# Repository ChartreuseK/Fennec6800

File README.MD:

# Fennec 6800
A Motorola 6800 Based Expandable Single Board Computer

## Introduction
The Fennec 6800 is a Motorola 6800 based single board computer (SBC) created with the inspiration of targeting 1977 components and features. It features an original Motorola 6800 processor running at whopping 921.6kHz, 8kB of the latest 2114 SRAM, 2kB of ROM using the brand new 2716 EPROM, and dual serial ports. An optional 40 pin expansion bus allows for connectivity to other modules, such as the Fennec VTI video terminal interface board, or to create your own attachments.

## Specifications
* Motorola 6800 @ 921.6kHz
* 1-8kB of onboard SRAM using pairs of 2114 (1k x 4 bit) SRAM chips. Using the optional RAM adapter board up to 32kB of RAM can be fitted with minimal modifications
* 2kB, 2716 EPROM containing the Fennec Monitor. Optional support for a 4kB 2732 EPROM
* Dual 6850 ACIA, RS-232 UART connected to dual 25 pin EIA-232 ports in DTE wiring.
* Selectable serial baud rates via DIP switches from 600-9600 baud + 115,200 in default /16 mode, 150-2400+28,800 in /64 mode when configured. Non-standard baud rates are possible using a different master oscillator, but CPU speed will be affected.
* Single rail design. Requires only a 5v regulated source of power.
* 40 pin expansion bus with pre-decoded expansion board select signals, allowing for quite prototyping of custom expansions.
* Beautiful blue PCB with exposed traces for a refined look.
* Compact Board design, only 8.6×5.2 inches!

The Fennec 6800 includes a capable and expandable ROM monitor built in, requiring no tedious toggling of front panel switches to enter and begin executing code. Only a terminal is required to begin making use of the system, simply hook the terminal up to the bottom serial port (furthest from the power jack). This serial port is the local console port in the default system, all traffic is normally routed through this port, though inside the monitor certain commands may be redirected to the auxiliary port located above it.

The monitor provides facilities for examining memory, depositing values into memory, jumping to code in memory, receiving a binary over the XMODEM protocol into RAM, and dumping a block of RAM over the XMODEM protocol. With these facilities and an appropriate host system, program development can be done remotely and loaded into the Fennec to speed up initial system bring-up and testing, or development can be done in the traditional way on paper then loaded in in hexadecimal into the program memory and tested out using the computer.

The monitor also provides support for option ROMs. These option ROM images can be mapped into any of the expansion regions in upper memory starting at a multiple of 0x1000. If detected they can hook into the monitor to provide future expandability and extra features, such as the Fennec VTI board which uses an option ROM to redirect the default terminal from the first serial port to a video display and asci keyboard interface, allowing for standalone use. Future cards may also use this facility to add additional commands such as providing for a rudimentary disk operation system for example.

## Manual
The file Fennec6800_Manual.pdf contains a more comprehensive manual of the Fennec, including some theory of operation as well as assembly hints and guides. Importantly if building a REV 0 board the bodeges required for correct operation are described. The primary bodge required is changing how the data bus buffer is selected, instead of being controlled by only the CPU it is decoded in a way to allow expansion boards to enable the buffer. The KiCAD schematics reflect the changes already made, however the gerbers and rev0 pcb file don't contain the fix.

## BOM 
The complete BOM can be found in either the manual, or in the spreadsheet Fennec6800_BOM.csv 
The BOM contains the reference designators, quantity, a description of the part, as well as one or more suitable Digikey part numbers. The CPU, ACIA/UARTs, and 2716/28C16 EPROM/EEPROM however need to be aquired from secondary sources as they have not been manufactured in some time. The CPU needs to be a MC6800 or direct compatible, note a 6802 has a different pinout and is not drop in compatible. The ACIAs are MC68B50 or similar UARTs, the B variant is not needed for the lower speeds, however a Hitachi 63B50 (2MHz rated) would be required for 115,200 board operation to not be overclocking the chip slightly. This speed however is honestly faster than the Fennec 68000 is really designed for, and at 9600 baud any variant is fine. For the EPROM any speed grade 2716 or 28C16 or equivalent 2kB (8-bit) EPROM/EEPROM is suitable. 2732 EPROMs may also be used, and the extra space can be mapped by installing the jumper next to the ROM socket, however the monitor would need to be reassembled to take advantage of the extra space.

## Burning the ROM
The 2716 EPROM on the Fennec 6800 should be burned with the file `software/monitor/monitor.bin`. This file is in a flat binary format suitable for burning onto a 2kB EPROM. If your program needs Intel HEX or Motorola SREC format it will need to be converted first. The ORG address is F800 (upper 2kB of address space). 

2716 EPROMs are single supply EPROMs, however they need a programmer capable of a 26v programming voltage. The common TL866CS/A is only capable of 21v, and the newer TL866II+ is only capable of 18v max, and won't be able to program the EPROM. For a more convient option there exists the 28C16 EEPROM which is pin compatible and can be programmed with only 5v and is suitable for either TL866 programmer, or even possibly with an Arduino and some custom code. The 28C16 is no-longer newly manufactured but can be fairly readilly sourced. Alternatively using a pin adapter a 28-pin 28C64 (still sold new on Digikey/Mouser from Atmel) can be converted to the 28C16 24-pin pinout. 

## Assembling the Monitor
The monitor source code is designed to be assembled with the cross-platform [AS macro assembler](http://john.ccac.rwth-aachen.de:8000/as/). It may be possible to assemble with other assemblers supporting the 6800, but some changes to the local label syntax may be required. The output of the macro assembler is it's own p file format which can then be converted using p2bin or p2hex to a suitable output format.

    asl -L monitor.asm && p2bin monitor.p
## Expansions

### 62256 RAM Adapter
In the folder Fennec 62256 RAM Adapter you can find a second PCB which allows the use of common and still in production 62256 (32k x 8) SRAM chips in place of the vintage and hard to source 2114 sram that the Fennec is designed for. This board slots into the top two ram sockets as well as the 74LS138 socket to provide the full 8kB of RAM that the board is designed for. Optionally A13 and A14 may be run to this adapter board to give the Fennec 32kB of RAM, more than normally designed for. 

### Fennec VTI
The [Fennec VTI](https://github.com/ChartreuseK/Fennec6800_VTI) is a 64x16 line text terminal interface with parallel ascii keyboard to provide a local terminal for the Fennec. It negates the need for an external serial terminal, or terminal emulator, making the Fennec into a self contained system. Using the extra port on the PIA on this card, combined with protoboard space, also allows it to be used for experimentations and developing hardware.

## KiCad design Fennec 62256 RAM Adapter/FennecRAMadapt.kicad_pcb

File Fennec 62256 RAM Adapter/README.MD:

# Fennec 6800 62256 RAM Adapter

This adapter allows the use of common 62256 32k x 8-bit SRAM chips with the Fennec 6800, replacing the vintage 2114 SRAM chips. The adapter plugs into the top two SRAM sockets as well as the 74LS138 socket (replacing the IC) and provides a full 8kB of SRAM to the Fennec. Optionally wires may be soldered down to the main board to grab A13 and A14 and soldered to the ram adapter. This modification would allow for the maximum of 32kB of RAM to be fitted to the system, more than normally possbile.

BOM:

* 1x 62256 SRAM - DIP 28
* 1x 74LS02 - DIP 14
* 1x 74LS08 - DIP 14
* 3x 0.1uF 50v X7R Ceramic Capacitors 0.1" pin spacing
* 2x 1k ohm 1/4W carbon film resistor, through hole
* 2x 1x40 pin male machine pin breakaway header. 
  * (16 + 18 + 18 + 9) = 61 pins required.
* Optional 1x40 male square pin header for jumpers. 2 + 3 + 3
* Optional 3x jumper shorting connectors
* 2x DIP 14 socket
* 1x DIP 28 wide (0.6") socket

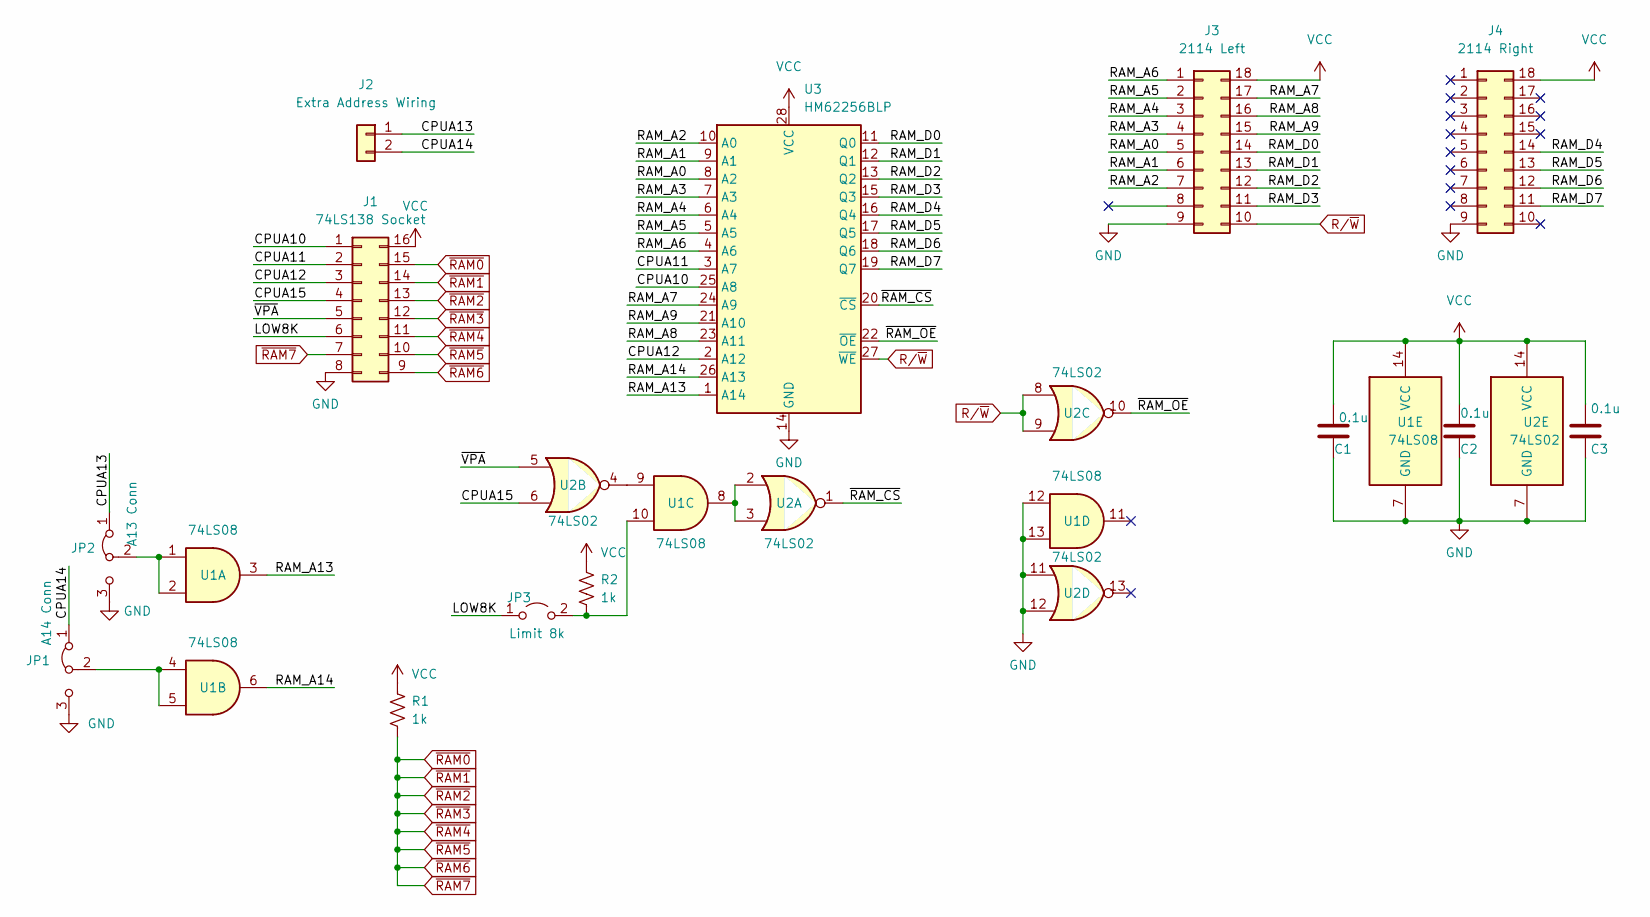
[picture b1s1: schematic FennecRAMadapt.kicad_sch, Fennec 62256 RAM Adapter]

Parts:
C1, C2, C3: 0.1u; C_Disc_D3.0mm_W1.6mm_P2.50mm
J1: 74LS138 Socket; DIP-16 Copper Ref Pin 1 Mark
J2: Extra Address Wiring; PinHeader_1x02_P2.54mm_Vertical
J3: 2114 Left; DIP-18 Copper Ref Pin 1 Mark
J4: 2114 Right; DIP-18 Copper Ref Pin 1 Mark
JP1: A14 Conn; PinHeader_1x03_P2.54mm_Vertical
JP2: A13 Conn; PinHeader_1x03_P2.54mm_Vertical
JP3: Limit 8k; PinHeader_1x02_P2.54mm_Vertical
R1, R2: 1k; R_Axial_DIN0207_L6.3mm_D2.5mm_P10.16mm_Horizontal
U1: 74LS08; DIP-14 Copper Ref Pin 1 Mark
U2: 74LS02; DIP-14 Copper Ref Pin 1 Mark
U3: HM62256BLP; DIP-28 Copper Ref Pin 1

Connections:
/CPUA10: J1.1, U3.25 (A8)
/CPUA11: J1.2, U3.3 (A7)
/CPUA12: J1.3, U3.2 (A12)
/CPUA13: J2.1, JP2.1 (A)
/CPUA14: J2.2, JP1.1 (A)
/CPUA15: J1.4, U2.6
/LOW8K: J1.6, JP3.1 (A); also elsewhere on the board
/RAM_A0: J3.5, U3.8 (A2)
/RAM_A1: J3.6, U3.9 (A1)
/RAM_A2: J3.7, U3.10 (A0)
/RAM_A3: J3.4, U3.7 (A3)
/RAM_A4: J3.3, U3.6 (A4)
/RAM_A5: J3.2, U3.5 (A5)
/RAM_A6: J3.1, U3.4 (A6)
/RAM_A7: J3.17, U3.24 (A9)
/RAM_A8: J3.16, U3.23 (A11)
/RAM_A9: J3.15, U3.21 (A10)
/RAM_A13: U1.3, U3.1 (A14)
/RAM_A14: U1.6, U3.26 (A13)
/RAM_D0: J3.14, U3.11 (Q0)
/RAM_D1: J3.13, U3.12 (Q1)
/RAM_D2: J3.12, U3.13 (Q2)
/RAM_D3: J3.11, U3.15 (Q3)
/RAM_D4: J4.14, U3.16 (Q4)
/RAM_D5: J4.13, U3.17 (Q5)
/RAM_D6: J4.12, U3.18 (Q6)
/RAM_D7: J4.11, U3.19 (Q7)
/~RAM_CS: U2.1, U3.20 (~CS)
/~RAM_OE: U2.10, U3.22 (~OE)
/~VPA: J1.5, U2.5
GND: C1.2, C2.2, C3.2, J1.8, J3.9, J4.9, JP1.3 (B), JP2.3 (B), U1.7 (GND), U1.12, U1.13, U2.7 (GND), U2.11, U2.12, U3.14 (GND)
unnamed: JP1.2 (C), U1.4, U1.5
unnamed: JP2.2 (C), U1.1, U1.2
unnamed 33: JP3.2 (B), R2.2, U1.10; also elsewhere on the board
unnamed: U1.8, U2.2, U2.3
unnamed: U1.9, U2.4
R/~W: J3.10, U2.8, U2.9, U3.27 (~WE)
VCC: C1.1, C2.1, C3.1, J1.16, J3.18, J4.18, R1.1, R2.1, U1.14 (VCC), U2.14 (VCC), U3.28 (VCC)
~RAM7: J1.7, J1.9, J1.10, J1.11, J1.12, J1.13, J1.14, J1.15, R1.2

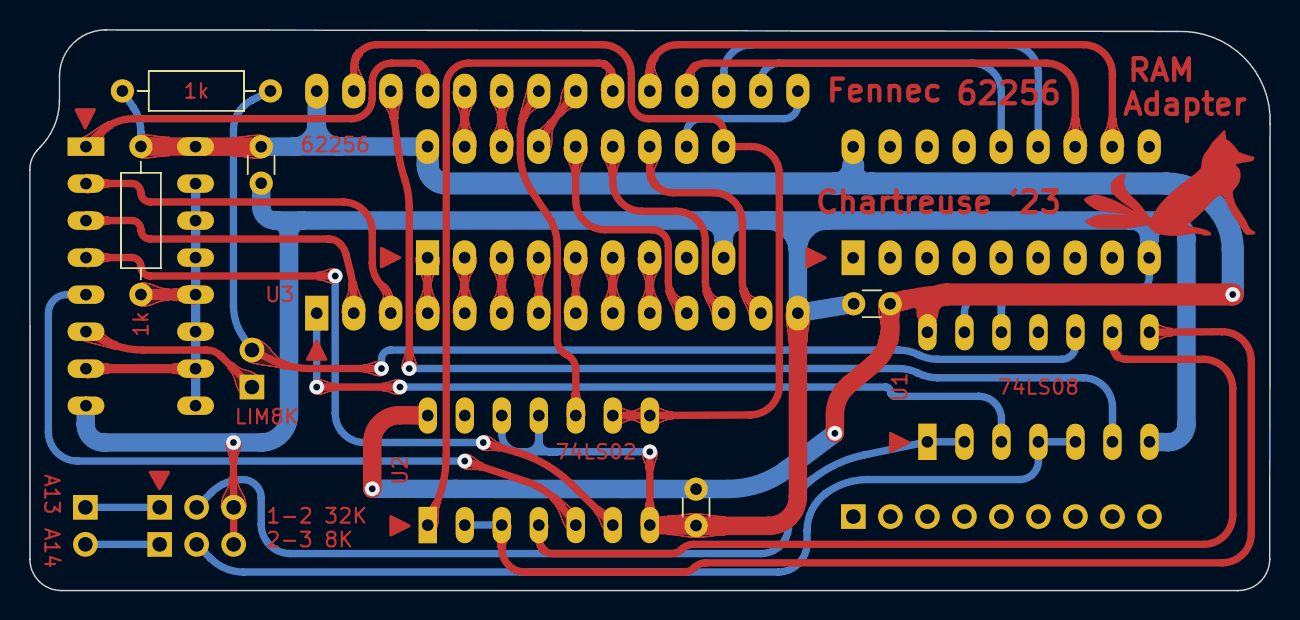
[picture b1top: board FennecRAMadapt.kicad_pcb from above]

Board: 2 copper layers, 85.1 x 38.5 mm, 16 parts (0 on the bottom side), 39 nets.

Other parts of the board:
LIM8K: Limit 8k; PinHeader_1x02_P2.54mm_Vertical
P1: Mounting Support DNC; PinHeader_1x09_P2.54mm_Vertical

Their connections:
/LOW8K: LIM8K.1 (A); also elsewhere on the board
unnamed 33: LIM8K.2 (B); also elsewhere on the board

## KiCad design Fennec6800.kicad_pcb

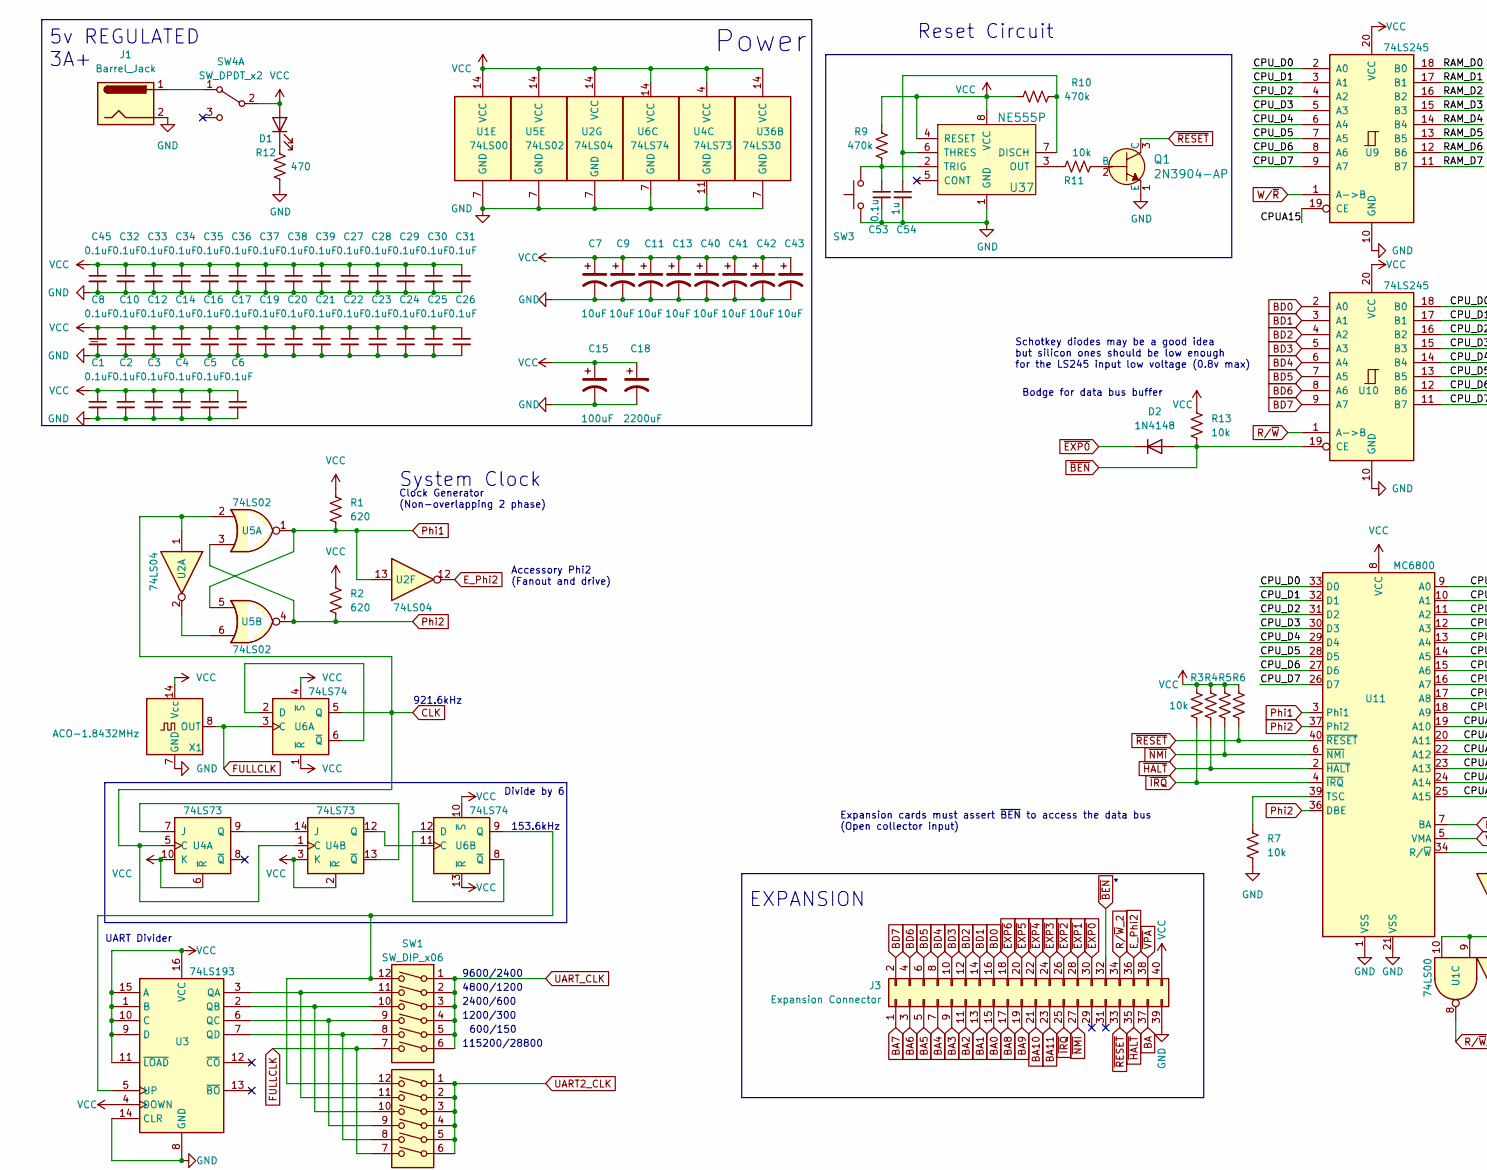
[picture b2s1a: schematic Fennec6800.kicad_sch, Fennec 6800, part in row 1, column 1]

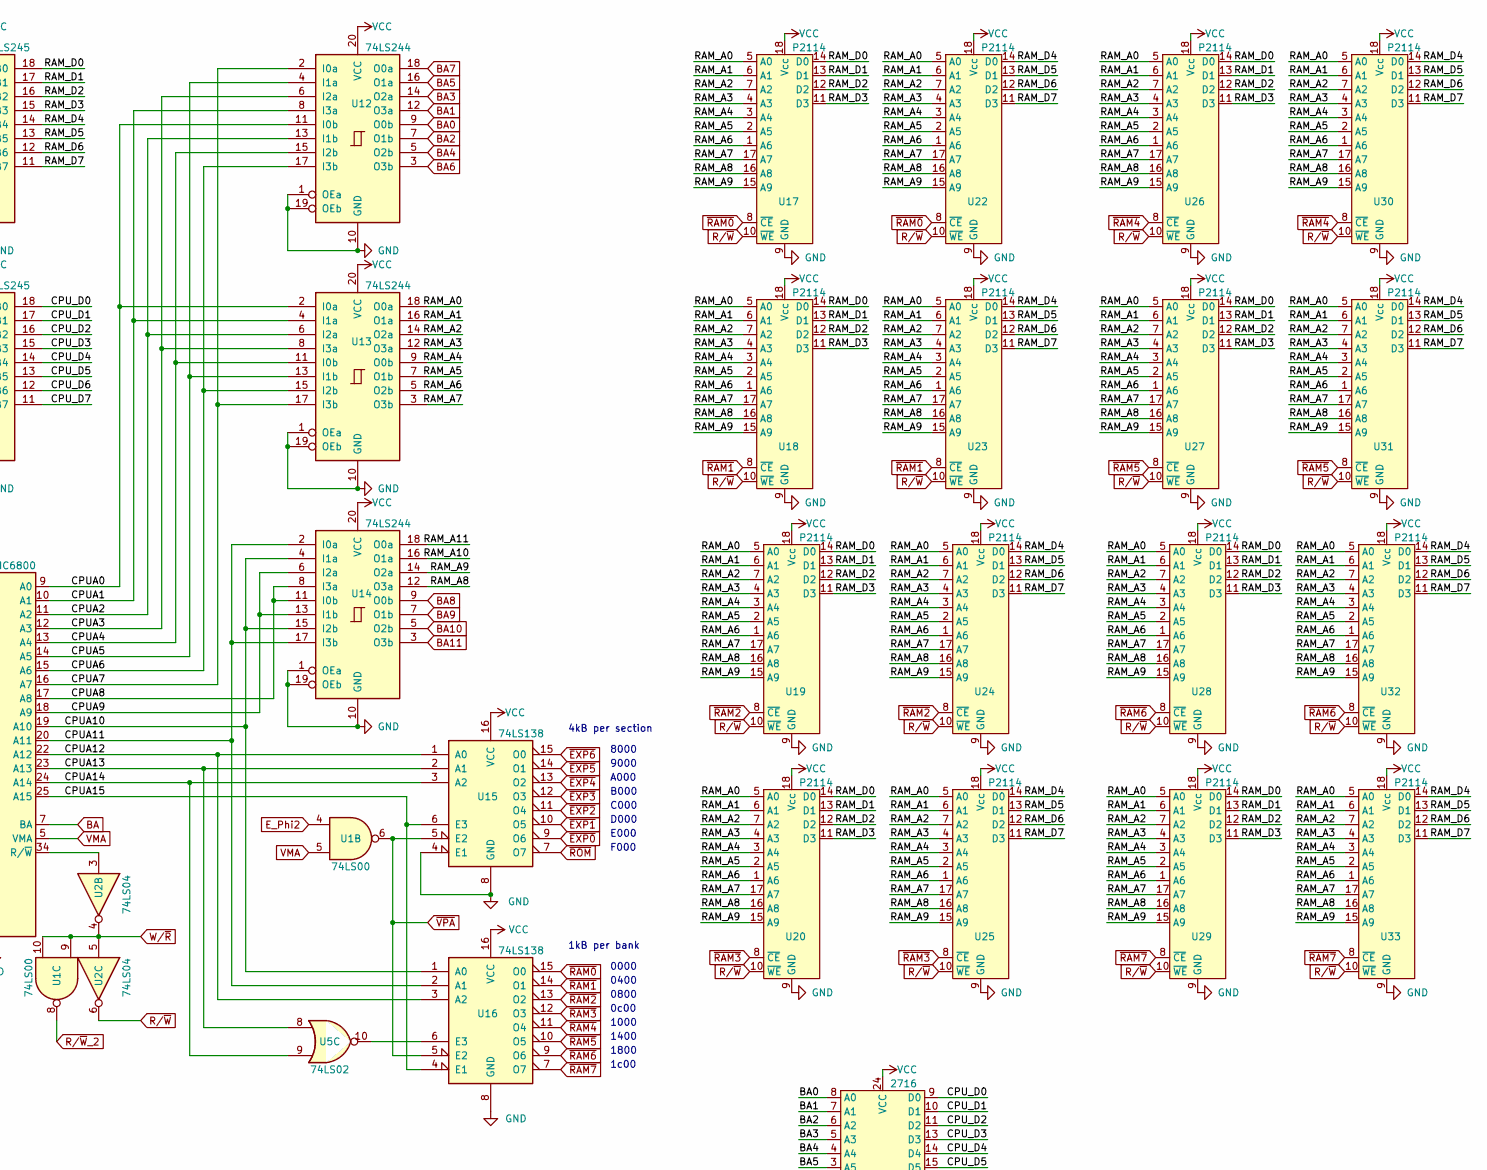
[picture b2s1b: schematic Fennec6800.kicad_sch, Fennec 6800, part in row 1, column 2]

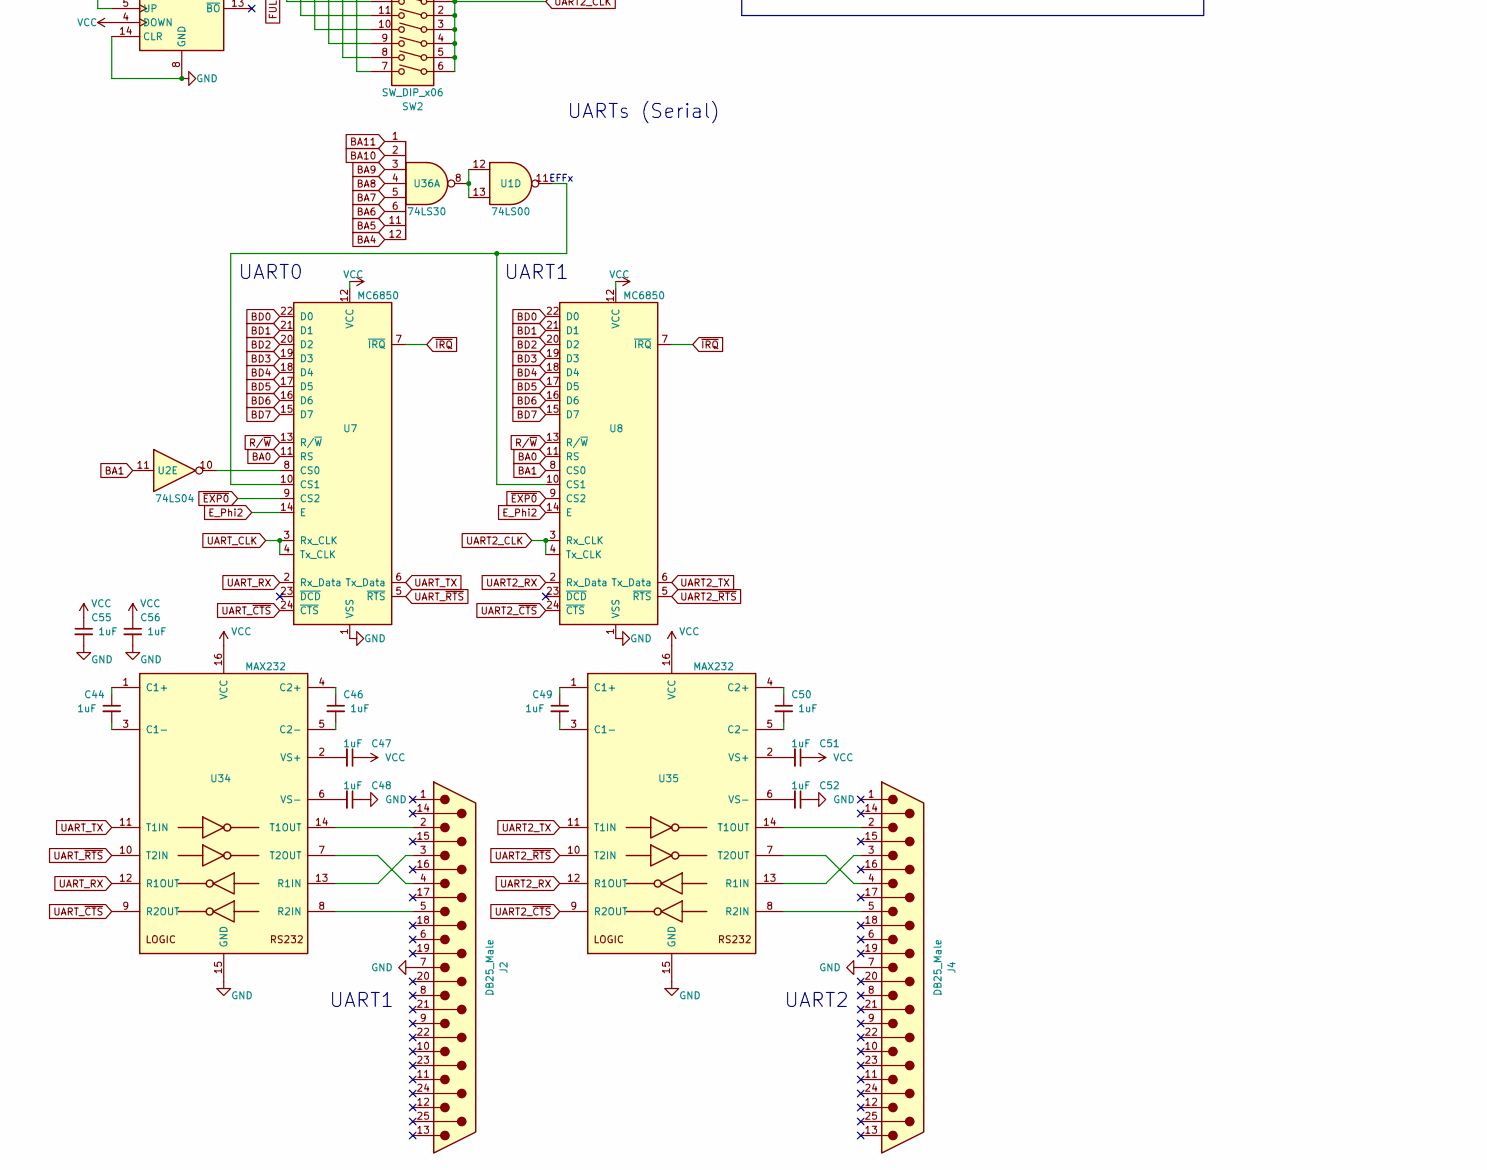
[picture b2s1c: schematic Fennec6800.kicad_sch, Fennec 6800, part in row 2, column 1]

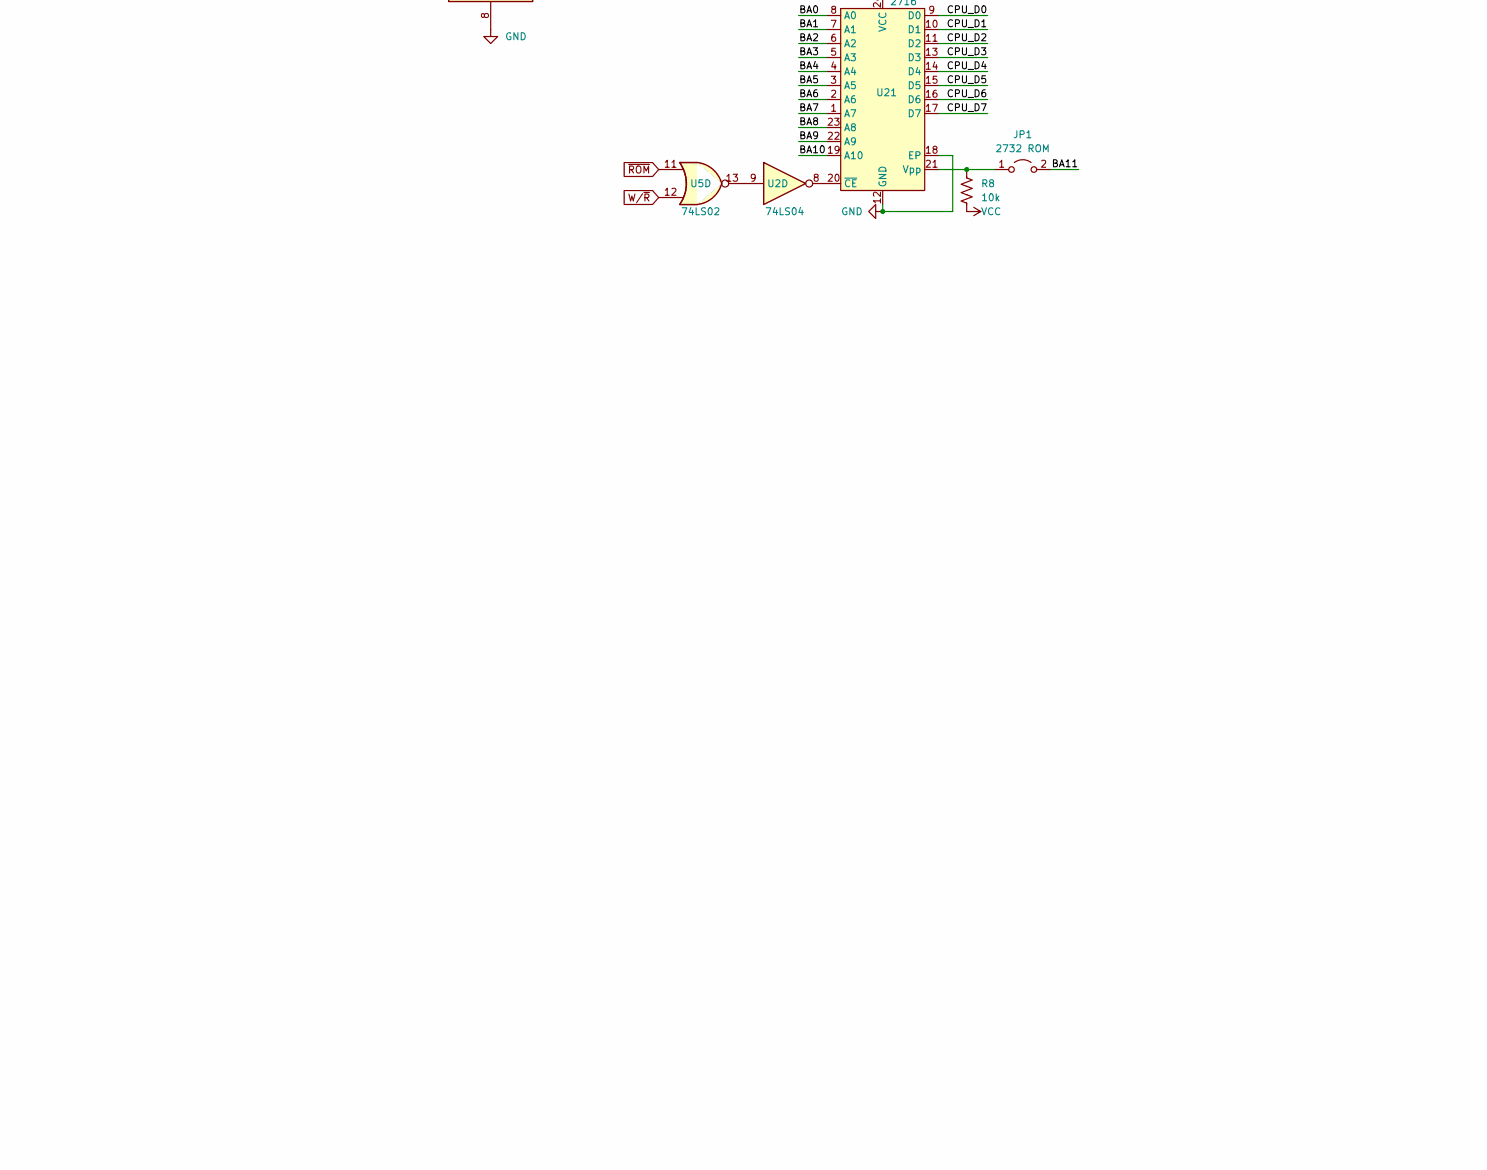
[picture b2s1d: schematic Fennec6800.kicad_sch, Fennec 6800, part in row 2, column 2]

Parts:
C1, C2, C3, C4, C5, C6, C8, C10, C12, C14, C16, C17, C19, C20, C21, C22, C23, C24, C25, C26, C27, C28, C29, C30, C31, C32, C33, C34, C35, C36, C37, C38, C39, C45: 0.1uF; C_Disc_D3.8mm_W2.6mm_P2.50mm
C7, C9, C11, C13, C40, C41, C42, C43: 10uF; CP_Radial_Tantal_D4.5mm_P2.50mm
C15: 100uF; CP_Radial_D6.3mm_P2.50mm
C18: 2200uF; CP_Radial_D12.5mm_P5.00mm
C44, C46, C47, C48, C49, C50, C51, C52, C55, C56: 1uF; C_Disc_D3.8mm_W2.6mm_P2.50mm
C53: 0.1u; C_Rect_L4.0mm_W2.5mm_P2.50mm
C54: 1u; C_Rect_L4.0mm_W2.5mm_P2.50mm
D1: LED; LED_D5.0mm
D2: 1N4148
J1: Barrel_Jack; BarrelJack_Horizontal
J2, J4: DB25_Male; DSUB-25_Male_Horizontal_P2.77x2.84mm_EdgePinOffset7.70mm_Ho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
J3: Expansion Connector; PinHeader_2x20_P2.54mm_Vertical
JP1: 2732 ROM; PinHeader_1x02_P2.54mm_Vertical
Q1: 2N3904-AP; TO-92; MPN 2N3904-AP; Digi-Key_PN 2N3904-APCT-ND
R1, R2: 620; R_Axial_DIN0207_L6.3mm_D2.5mm_P10.16mm_Horizontal
R3, R4, R5, R6, R7, R8, R13: 10k; R_Axial_DIN0207_L6.3mm_D2.5mm_P10.16mm_Horizontal
R9, R10: 470k; R_Axial_DIN0207_L6.3mm_D2.5mm_P2.54mm_Vertical
R11: 10k; R_Axial_DIN0207_L6.3mm_D2.5mm_P2.54mm_Vertical
R12: 470; R_Axial_DIN0207_L6.3mm_D2.5mm_P10.16mm_Horizontal
SW1, SW2: SW_DIP_x06; SW_DIP_SPSTx06_Slide_9.78x17.42mm_W7.62mm_P2.54mm
SW3: SW_Push; SW_PUSH_6mm
SW4: SW_DPDT_x2; VerticalToggle_ESWITCH_100SP1T2B4M7QE
U1: 74LS00; DIP-14_W7.62mm_Socket_LongPads
U2: 74LS04; DIP-14_W7.62mm_Socket_LongPads
U3: 74LS193; DIP-16_W7.62mm_Socket_LongPads
U4: 74LS73; DIP-14_W7.62mm_Socket_LongPads
U5: 74LS02; DIP-14_W7.62mm_Socket_LongPads
U6: 74LS74; DIP-14_W7.62mm_Socket_LongPads
U7, U8: MC6850; DIP-24_W15.24mm_Socket_LongPads
U9, U10: 74LS245; DIP-20_W7.62mm_Socket_LongPads
U11: MC6800; DIP-40_W15.24mm_Socket_LongPads
U12, U13, U14: 74LS244; DIP-20_W7.62mm_Socket_LongPads
U15, U16: 74LS138; DIP-16_W7.62mm_Socket_LongPads
U17, U18, U19, U20, U22, U23, U24, U25, U26, U27, U28, U29, U30, U31, U32, U33: P2114; DIP-18_W7.62mm_Socket_LongPads
U21: 2716; DIP-24_W15.24mm_Socket_LongPads
U34, U35: MAX232; DIP-16_W7.62mm_Socket_LongPads
U36: 74LS30; DIP-14_W7.62mm_Socket_LongPads
U37: NE555P; DIP-8_W7.62mm_Socket_LongPads; MPN NE555P; Digi-Key_PN 296-1411-5-ND
X1: ACO-1.8432MHz; Oscillator_DIP-14

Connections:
/CPUA0: U11.9 (A0), U12.11 (I0b), U13.2 (I0a)
/CPUA1: U11.10 (A1), U12.8 (I3a), U13.4 (I1a)
/CPUA2: U11.11 (A2), U12.13 (I1b), U13.6 (I2a)
/CPUA3: U11.12 (A3), U12.6 (I2a), U13.8 (I3a)
/CPUA4: U11.13 (A4), U12.15 (I2b), U13.11 (I0b)
/CPUA5: U11.14 (A5), U12.4 (I1a), U13.13 (I1b)
/CPUA6: U11.15 (A6), U12.17 (I3b), U13.15 (I2b)
/CPUA7: U11.16 (A7), U12.2 (I0a), U13.17 (I3b)
/CPUA8: U11.17 (A8), U14.8 (I3a), U14.11 (I0b)
/CPUA9: U11.18 (A9), U14.6 (I2a), U14.13 (I1b)
/CPUA10: U11.19 (A10), U14.4 (I1a), U14.15 (I2b), U16.1 (A0)
/CPUA11: U11.20 (A11), U14.2 (I0a), U14.17 (I3b), U16.2 (A1)
/CPUA12: U11.22 (A12), U15.1 (A0), U16.3 (A2)
/CPUA13: U5.8, U11.23 (A13), U15.2 (A1)
/CPUA14: U5.9, U11.24 (A14), U15.3 (A2)
/CPU_D0: U9.2 (A0), U10.18 (B0), U11.33 (D0), U21.9 (D0)
/CPU_D1: U9.3 (A1), U10.17 (B1), U11.32 (D1), U21.10 (D1)
/CPU_D2: U9.4 (A2), U10.16 (B2), U11.31 (D2), U21.11 (D2)
/CPU_D3: U9.5 (A3), U10.15 (B3), U11.30 (D3), U21.13 (D3)
/CPU_D4: U9.6 (A4), U10.14 (B4), U11.29 (D4), U21.14 (D4)
/CPU_D5: U9.7 (A5), U10.13 (B5), U11.28 (D5), U21.15 (D5)
/CPU_D6: U9.8 (A6), U10.12 (B6), U11.27 (D6), U21.16 (D6)
/CPU_D7: U9.9 (A7), U10.11 (B7), U11.26 (D7), U21.17 (D7)
/RAM_A0: U13.18 (O0a), U17.5 (A0), U18.5 (A0), U19.5 (A0), U20.5 (A0), U22.5 (A0), U23.5 (A0), U24.5 (A0), U25.5 (A0), U26.5 (A0), U27.5 (A0), U28.5 (A0), U29.5 (A0), U30.5 (A0), U31.5 (A0), U32.5 (A0), U33.5 (A0)
/RAM_A1: U13.16 (O1a), U17.6 (A1), U18.6 (A1), U19.6 (A1), U20.6 (A1), U22.6 (A1), U23.6 (A1), U24.6 (A1), U25.6 (A1), U26.6 (A1), U27.6 (A1), U28.6 (A1), U29.6 (A1), U30.6 (A1), U31.6 (A1), U32.6 (A1), U33.6 (A1)
/RAM_A2: U13.14 (O2a), U17.7 (A2), U18.7 (A2), U19.7 (A2), U20.7 (A2), U22.7 (A2), U23.7 (A2), U24.7 (A2), U25.7 (A2), U26.7 (A2), U27.7 (A2), U28.7 (A2), U29.7 (A2), U30.7 (A2), U31.7 (A2), U32.7 (A2), U33.7 (A2)
/RAM_A3: U13.12 (O3a), U17.4 (A3), U18.4 (A3), U19.4 (A3), U20.4 (A3), U22.4 (A3), U23.4 (A3), U24.4 (A3), U25.4 (A3), U26.4 (A3), U27.4 (A3), U28.4 (A3), U29.4 (A3), U30.4 (A3), U31.4 (A3), U32.4 (A3), U33.4 (A3)
/RAM_A4: U13.9 (O0b), U17.3 (A4), U18.3 (A4), U19.3 (A4), U20.3 (A4), U22.3 (A4), U23.3 (A4), U24.3 (A4), U25.3 (A4), U26.3 (A4), U27.3 (A4), U28.3 (A4), U29.3 (A4), U30.3 (A4), U31.3 (A4), U32.3 (A4), U33.3 (A4)
/RAM_A5: U13.7 (O1b), U17.2 (A5), U18.2 (A5), U19.2 (A5), U20.2 (A5), U22.2 (A5), U23.2 (A5), U24.2 (A5), U25.2 (A5), U26.2 (A5), U27.2 (A5), U28.2 (A5), U29.2 (A5), U30.2 (A5), U31.2 (A5), U32.2 (A5), U33.2 (A5)
/RAM_A6: U13.5 (O2b), U17.1 (A6), U18.1 (A6), U19.1 (A6), U20.1 (A6), U22.1 (A6), U23.1 (A6), U24.1 (A6), U25.1 (A6), U26.1 (A6), U27.1 (A6), U28.1 (A6), U29.1 (A6), U30.1 (A6), U31.1 (A6), U32.1 (A6), U33.1 (A6)
/RAM_A7: U13.3 (O3b), U17.17 (A7), U18.17 (A7), U19.17 (A7), U20.17 (A7), U22.17 (A7), U23.17 (A7), U24.17 (A7), U25.17 (A7), U26.17 (A7), U27.17 (A7), U28.17 (A7), U29.17 (A7), U30.17 (A7), U31.17 (A7), U32.17 (A7), U33.17 (A7)
/RAM_A8: U14.12 (O3a), U17.16 (A8), U18.16 (A8), U19.16 (A8), U20.16 (A8), U22.16 (A8), U23.16 (A8), U24.16 (A8), U25.16 (A8), U26.16 (A8), U27.16 (A8), U28.16 (A8), U29.16 (A8), U30.16 (A8), U31.16 (A8), U32.16 (A8), U33.16 (A8)
/RAM_A9: U14.14 (O2a), U17.15 (A9), U18.15 (A9), U19.15 (A9), U20.15 (A9), U22.15 (A9), U23.15 (A9), U24.15 (A9), U25.15 (A9), U26.15 (A9), U27.15 (A9), U28.15 (A9), U29.15 (A9), U30.15 (A9), U31.15 (A9), U32.15 (A9), U33.15 (A9)
/RAM_A10: U14.16 (O1a)
/RAM_A11: U14.18 (O0a)
/RAM_D0: U9.18 (B0), U17.14 (D0), U18.14 (D0), U19.14 (D0), U20.14 (D0), U26.14 (D0), U27.14 (D0), U28.14 (D0), U29.14 (D0)
/RAM_D1: U9.17 (B1), U17.13 (D1), U18.13 (D1), U19.13 (D1), U20.13 (D1), U26.13 (D1), U27.13 (D1), U28.13 (D1), U29.13 (D1)
/RAM_D2: U9.16 (B2), U17.12 (D2), U18.12 (D2), U19.12 (D2), U20.12 (D2), U26.12 (D2), U27.12 (D2), U28.12 (D2), U29.12 (D2)
/RAM_D3: U9.15 (B3), U17.11 (D3), U18.11 (D3), U19.11 (D3), U20.11 (D3), U26.11 (D3), U27.11 (D3), U28.11 (D3), U29.11 (D3)
/RAM_D4: U9.14 (B4), U22.14 (D0), U23.14 (D0), U24.14 (D0), U25.14 (D0), U30.14 (D0), U31.14 (D0), U32.14 (D0), U33.14 (D0)
/RAM_D5: U9.13 (B5), U22.13 (D1), U23.13 (D1), U24.13 (D1), U25.13 (D1), U30.13 (D1), U31.13 (D1), U32.13 (D1), U33.13 (D1)
/RAM_D6: U9.12 (B6), U22.12 (D2), U23.12 (D2), U24.12 (D2), U25.12 (D2), U30.12 (D2), U31.12 (D2), U32.12 (D2), U33.12 (D2)
/RAM_D7: U9.11 (B7), U22.11 (D3), U23.11 (D3), U24.11 (D3), U25.11 (D3), U30.11 (D3), U31.11 (D3), U32.11 (D3), U33.11 (D3)
BA: J3.37, U11.7 (BA)
BA0: J3.15, U7.11 (RS), U8.11 (RS), U12.9 (O0b), U21.8 (A0)
BA1: J3.13, U2.11, U8.8 (CS0), U12.12 (O3a), U21.7 (A1)
BA2: J3.11, U12.7 (O1b), U21.6 (A2)
BA3: J3.9, U12.14 (O2a), U21.5 (A3)
BA4: J3.7, U12.5 (O2b), U21.4 (A4), U36.12
BA5: J3.5, U12.16 (O1a), U21.3 (A5), U36.11
BA6: J3.3, U12.3 (O3b), U21.2 (A6), U36.6
BA7: J3.1, U12.18 (O0a), U21.1 (A7), U36.5
BA8: J3.17, U14.9 (O0b), U21.23 (A8), U36.4
BA9: J3.19, U14.7 (O1b), U21.22 (A9), U36.3
BA10: J3.21, U14.5 (O2b), U21.19 (A10), U36.2
BA11: J3.23, JP1.2 (B), U14.3 (O3b), U36.1
BD0: J3.16, U7.22 (D0), U8.22 (D0), U10.2 (A0)
BD1: J3.14, U7.21 (D1), U8.21 (D1), U10.3 (A1)
BD2: J3.12, U7.20 (D2), U8.20 (D2), U10.4 (A2)
BD3: J3.10, U7.19 (D3), U8.19 (D3), U10.5 (A3)
BD4: J3.8, U7.18 (D4), U8.18 (D4), U10.6 (A4)
BD5: J3.6, U7.17 (D5), U8.17 (D5), U10.7 (A5)
BD6: J3.4, U7.16 (D6), U8.16 (D6), U10.8 (A6)
BD7: J3.2, U7.15 (D7), U8.15 (D7), U10.9 (A7)
unnamed: C44.1, U34.1 (C1+)
unnamed: C44.2, U34.3 (C1-)
unnamed: C46.1, U34.4 (C2+)
unnamed: C46.2, U34.5 (C2-)
unnamed: C47.2, U34.2 (VS+)
unnamed: C48.2, U34.6 (VS-)
unnamed: C49.1, U35.1 (C1+)
unnamed: C49.2, U35.3 (C1-)
unnamed: C50.1, U35.4 (C2+)
unnamed: C50.2, U35.5 (C2-)
unnamed: C51.2, U35.2 (VS+)
unnamed: C52.2, U35.6 (VS-)
unnamed: C53.1, R9.2, SW3.2, U37.2 (TRIG)
unnamed: C54.1, R10.1, U37.6 (THRES), U37.7 (DISCH)
unnamed: J1.1, SW4.1 (A)
unnamed: J2.2, U34.14 (T1OUT)
unnamed: J2.3, U34.13 (R1IN)
unnamed: J2.4, U34.7 (T2OUT)
unnamed: J2.5, U34.8 (R2IN)
unnamed: J4.2, U35.14 (T1OUT)
unnamed: J4.3, U35.13 (R1IN)
unnamed: J4.4, U35.7 (T2OUT)
unnamed: J4.5, U35.8 (R2IN)
unnamed: JP1.1 (A), R8.2, U21.21 (Vpp)
unnamed: Q1.2 (B), R11.2
unnamed: R7.1, U11.39 (TSC)
unnamed: R11.1, U37.3 (OUT)
unnamed: SW1.8, SW2.8, U3.7 (QD)
unnamed: SW1.9, SW2.9, U3.6 (QC)
unnamed: SW1.10, SW2.10, U3.2 (QB)
unnamed: SW1.11, SW2.11, U3.3 (QA)
unnamed: SW1.12, SW2.12, U3.5 (UP), U6.9 (Q)
unnamed: U1.11, U7.10 (CS1), U8.10 (CS1)
unnamed: U1.12, U1.13, U36.8
unnamed: U2.2, U5.6
unnamed: U2.8, U21.20 (~CE)
unnamed: U2.9, U5.13
unnamed: U2.10, U7.8 (CS0)
unnamed: U4.12 (Q), U6.11 (C)
unnamed: U4.7 (J), U4.13 (~Q)
unnamed: U4.9 (Q), U4.14 (J)
unnamed: U6.2 (D), U6.6 (~Q)
unnamed: U6.8 (~Q), U6.12 (D)
unnamed: U2.3, U11.34 (R/~W)
unnamed: U5.10, U16.6 (E3)
Phi1: R1.2, U2.13, U5.1, U5.5, U11.3 (Phi1)
Phi2: R2.2, U5.3, U5.4, U11.36 (DBE), U11.37 (Phi2)
R/~W: U2.6, U7.13 (R/~W), U8.13 (R/~W), U10.1 (A->B), U17.10 (~WE), U18.10 (~WE), U19.10 (~WE), U20.10 (~WE), U22.10 (~WE), U23.10 (~WE), U24.10 (~WE), U25.10 (~WE), U26.10 (~WE), U27.10 (~WE), U28.10 (~WE), U29.10 (~WE), U30.10 (~WE), U31.10 (~WE), U32.10 (~WE), U33.10 (~WE)
R/~W_2: J3.34, U1.8
UART2_CLK: SW2.1, SW2.2, SW2.3, SW2.4, SW2.5, SW2.6, U8.3 (Rx_CLK), U8.4 (Tx_CLK)
UART2_RX: U8.2 (Rx_Data), U35.12 (R1OUT)
UART2_TX: U8.6 (Tx_Data), U35.11 (T1IN)
UART2_~CTS: U8.24 (~CTS), U35.9 (R2OUT)
UART2_~RTS: U8.5 (~RTS), U35.10 (T2IN)
UART_CLK: SW1.1, SW1.2, SW1.3, SW1.4, SW1.5, SW1.6, U7.3 (Rx_CLK), U7.4 (Tx_CLK)
UART_RX: U7.2 (Rx_Data), U34.12 (R1OUT)
UART_TX: U7.6 (Tx_Data), U34.11 (T1IN)
UART_~CTS: U7.24 (~CTS), U34.9 (R2OUT)
UART_~RTS: U7.5 (~RTS), U34.10 (T2IN)
VMA: U1.5, U11.5 (VMA)
VPA: J3.38, U1.6, U15.5 (E2), U16.5 (E2)
W/~R: U1.9, U1.10, U2.4, U2.5, U5.12, U9.1 (A->B)
~EXP0: D2.1 (K), J3.30, U7.9 (CS2), U8.9 (CS2), U15.9 (O6)
~EXP1: J3.28, U15.10 (O5)
~EXP2: J3.26, U15.11 (O4)
~EXP3: J3.24, U15.12 (O3)
~EXP4: J3.22, U15.13 (O2)
~EXP5: J3.20, U15.14 (O1)
~EXP6: J3.18, U15.15 (O0)
~HALT: J3.35, R4.2, U11.2 (~HALT)
~IRQ: J3.25, R3.2, U7.7 (~IRQ), U8.7 (~IRQ), U11.4 (~IRQ)
~NMI: J3.27, R5.2, U11.6 (~NMI)
~RAM0: U16.15 (O0), U17.8 (~CE), U22.8 (~CE)
~RAM1: U16.14 (O1), U18.8 (~CE), U23.8 (~CE)
~RAM2: U16.13 (O2), U19.8 (~CE), U24.8 (~CE)
~RAM3: U16.12 (O3), U20.8 (~CE), U25.8 (~CE)
~RAM4: U16.11 (O4), U26.8 (~CE), U30.8 (~CE)
~RAM5: U16.10 (O5), U27.8 (~CE), U31.8 (~CE)
~RAM6: U16.9 (O6), U28.8 (~CE), U32.8 (~CE)
~RAM7: U16.7 (O7), U29.8 (~CE), U33.8 (~CE)
~RESET: J3.33, Q1.3 (C), R6.2, U11.40 (~RESET)
~ROM: U5.11, U15.7 (O7)

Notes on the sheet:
1200/300
9000
2400/600
Divide by 6
UART0
UARTs (Serial)
Expansion cards must assert ~{BEN} to access the data bus (Open collector input)
0800
Reset Circuit
4kB per section
C000
A000
1c00
UART1
8000
153.6kHz
Accessory Phi2 (Fanout and drive)
0c00
1800
1kB per bank
5v REGULATED 3A+
Bodge for data bus buffer
Schotkey diodes may be a good idea but silicon ones should be low enough for the LS245 input low voltage (0.8v max)
D000
E000
115200/28800
1400
UART Divider
921.6kHz
9600/2400
System Clock
EFFx
Power
600/150
0000
B000
EXPANSION
0400
Clock Generator (Non-overlapping 2 phase)
4800/1200

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
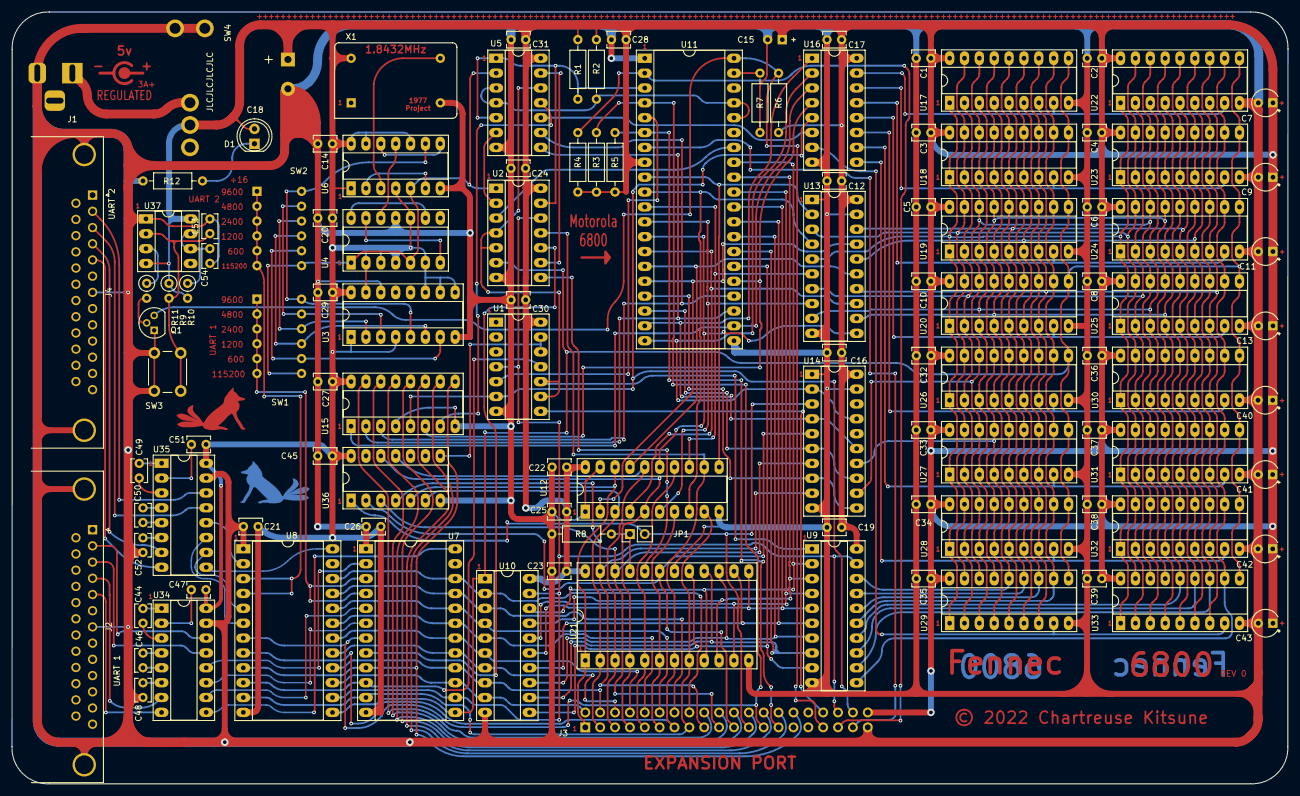
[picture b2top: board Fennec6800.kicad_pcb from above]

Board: 2 copper layers, 218.0 x 131.9 mm, 115 parts (0 on the bottom side), 151 nets.

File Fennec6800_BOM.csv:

Reference Designators,Qty.,Part,Digikey Part #,Alternative Digikey Part # (ICs are HCT instead of LS)
"C1, C2, C3, C4, C5, C6, C8, C10, C12, C14, C16, C17, C19, C20, C21, C22, C23, C24, C25, C26, C27, C28, C29, C30, C31, C32, C33, C34, C35, C36, C37, C38, C39, C45, C53",35,"0.1uF 50v Ceramic Capacitor, .1” pin pitch",399-14036-1-ND,
"C7, C9, C11, C13, C40, C41, C42, C43",8,"10uF 16v Tantalum Capacitor, .1” pin pitch",478-TAP106K016CRSCT-ND,
C15,1,"100uF 16v Aluminum Electrolytic. .1” pin pitch, diameter < 6.3mm",P19632CT-ND,
C18,1,"470uF 16v Aluminum Electrolytic. 5mm pin pitch, diameter <13mm",P12375-ND,
"C44, C46, C47, C48, C49, C50, C51, C52, C56, C55, C56",11,"1.0uF 50v X5R Ceramic Capactior, .1” pin pitch",445-173257-1-ND,478-11561-1-ND
D1,1,T1-3/4 (5mm) low-brightness red LED,160-1707-ND,
D2,1,1N4148 DO-3 diode,1N4148FS-ND,
J1,1,"Barrel_Jack, 2.1mm x 5.5mm",CP-202A-ND,CP-102A-ND
"J2, J4",2,"DB25 Male, right angle board mount. 7.7mm pin edge offset, 9.12mm mounting hole offset",2057-DB25-PL-24-ND,
J3,1,2x20 0.1” male pin header,10129381-940002BLF-ND,S2011EC-40-ND
JP1,1,1x2 0.1” male pin header,2057-PH1-02-UA-ND,S1011EC-40-ND
Q1,1,2N3904-AP TO-92 package with stagered center pin,2N3904BU,2N3904-AP
"R1, R2",2,620 ohm 1/4W 5% Carbon Film,620QBK-ND,
"R3, R4, R5, R6, R7, R8, R13",8,10k ohm 1/4W 5% Carbon Film,CF14JT10K0CT-ND,
"R9, R10",2,470k ohm 1/4W 5% Carbon Film,CF14JT470KCT-ND,
R12,1,470 ohm 1/4W 5% Carbon Film,CF14JT470RCT-ND,
"SW1, SW2",2,"DIP-12, 6 pole DIP switch, 0.3” spacing",2449-KG06E-ND ,
SW3,1,6mm through hole push button,679-2428-ND,
SW4,1,"ESWITCH 100SP1T2B4M7QE right angle toggle switch or compatible, SPDT switch",EG5419-ND,
U1,1,74LS00 DIP,296-1626-ND,296-1603-5-ND
U2,1,74LS04 DIP,296-1629-5-ND,296-1605-5-ND
U3,1,74LS193 DIP,296-1605-5-ND,296-2142-5-ND
U4,1,74LS73 DIP,296-26520-5-ND,296-3541-5-ND 
U5,1,74LS02 DIP,296-1627-5-ND,296-3541-5-ND 
U6,1,74LS74 DIP,296-1668-5-ND,296-1605-5-ND
"U7, U8",2,MC6850 (68A50/68B50/6350/63A50/63B50) DIP,"Vintage, eBay",
"U9, U10",2,74LS245 DIP,296-1655-5-ND,296-2105-5-ND
U11,1,MC6800 Microprocessor,"Vintage, eBay",
"U12, U13, U14",3,74LS244 DIP,296-1653-5-ND,296-1610-5-ND
"U15, U16",2,74LS138 DIP,296-1639-5-ND,296-1608-5-ND
"U17, U18, U19, U20, U22, U23, U24, U25, U26, U27, U28, U29, U30, U31, U32, U33",16,P2114 SRAM DIP-18,"Vintage, eBay",
U21,1,2716 EPROM or 28C16 EEPROM,"Vintage, eBay",
"U34, U35",2,MAX232ECN or similar DIP,296-26139-5-ND,
U36,1,74LS30 DIP,296-3693-5-ND,296-2111-5-ND
U37,1,NE555P DIP,296-NE555P-ND,ICM7555IPAZ-ND
X1,1,1.8432MHz Full-can (DIP-14) oscillator,X939-ND,110-MXO45-3C-1M843200-ND
,,,,
,,,,
,,,,
X1 Socket,1,DIP-14 (0.3”) crystal socket,ED90428-ND,
"U7, U8, U21 Socket",3,DIP-24 (0.6”) socket,1175-2554-ND,
"U9, U10, U12, U13, U14 Socket",5,DIP-20 (0.3”) socket,AE9998-ND,
U11 Socket,1,DIP-40 (0.6”) socket,ED3033-ND,
"U1, U2, U4, U5, U6, U36 Socket",6,DIP-14 (0.3”) socket,2057-ICS-314-T-ND,
"U3, U15, U16, U34, U45",5,DIP-16 (0.3”) socket,AE9992-ND,
"U17, U18, U19, U20, U22, U23, U24, U25, U26, U27, U28, U29, U30, U31, U32, U33 Socket",16,DIP-18 (0.3”) socket,2057-ICS-318-T-ND,

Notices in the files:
Fennec6800.kicad_pcb:
© 2022 Chartreuse Kitsune
